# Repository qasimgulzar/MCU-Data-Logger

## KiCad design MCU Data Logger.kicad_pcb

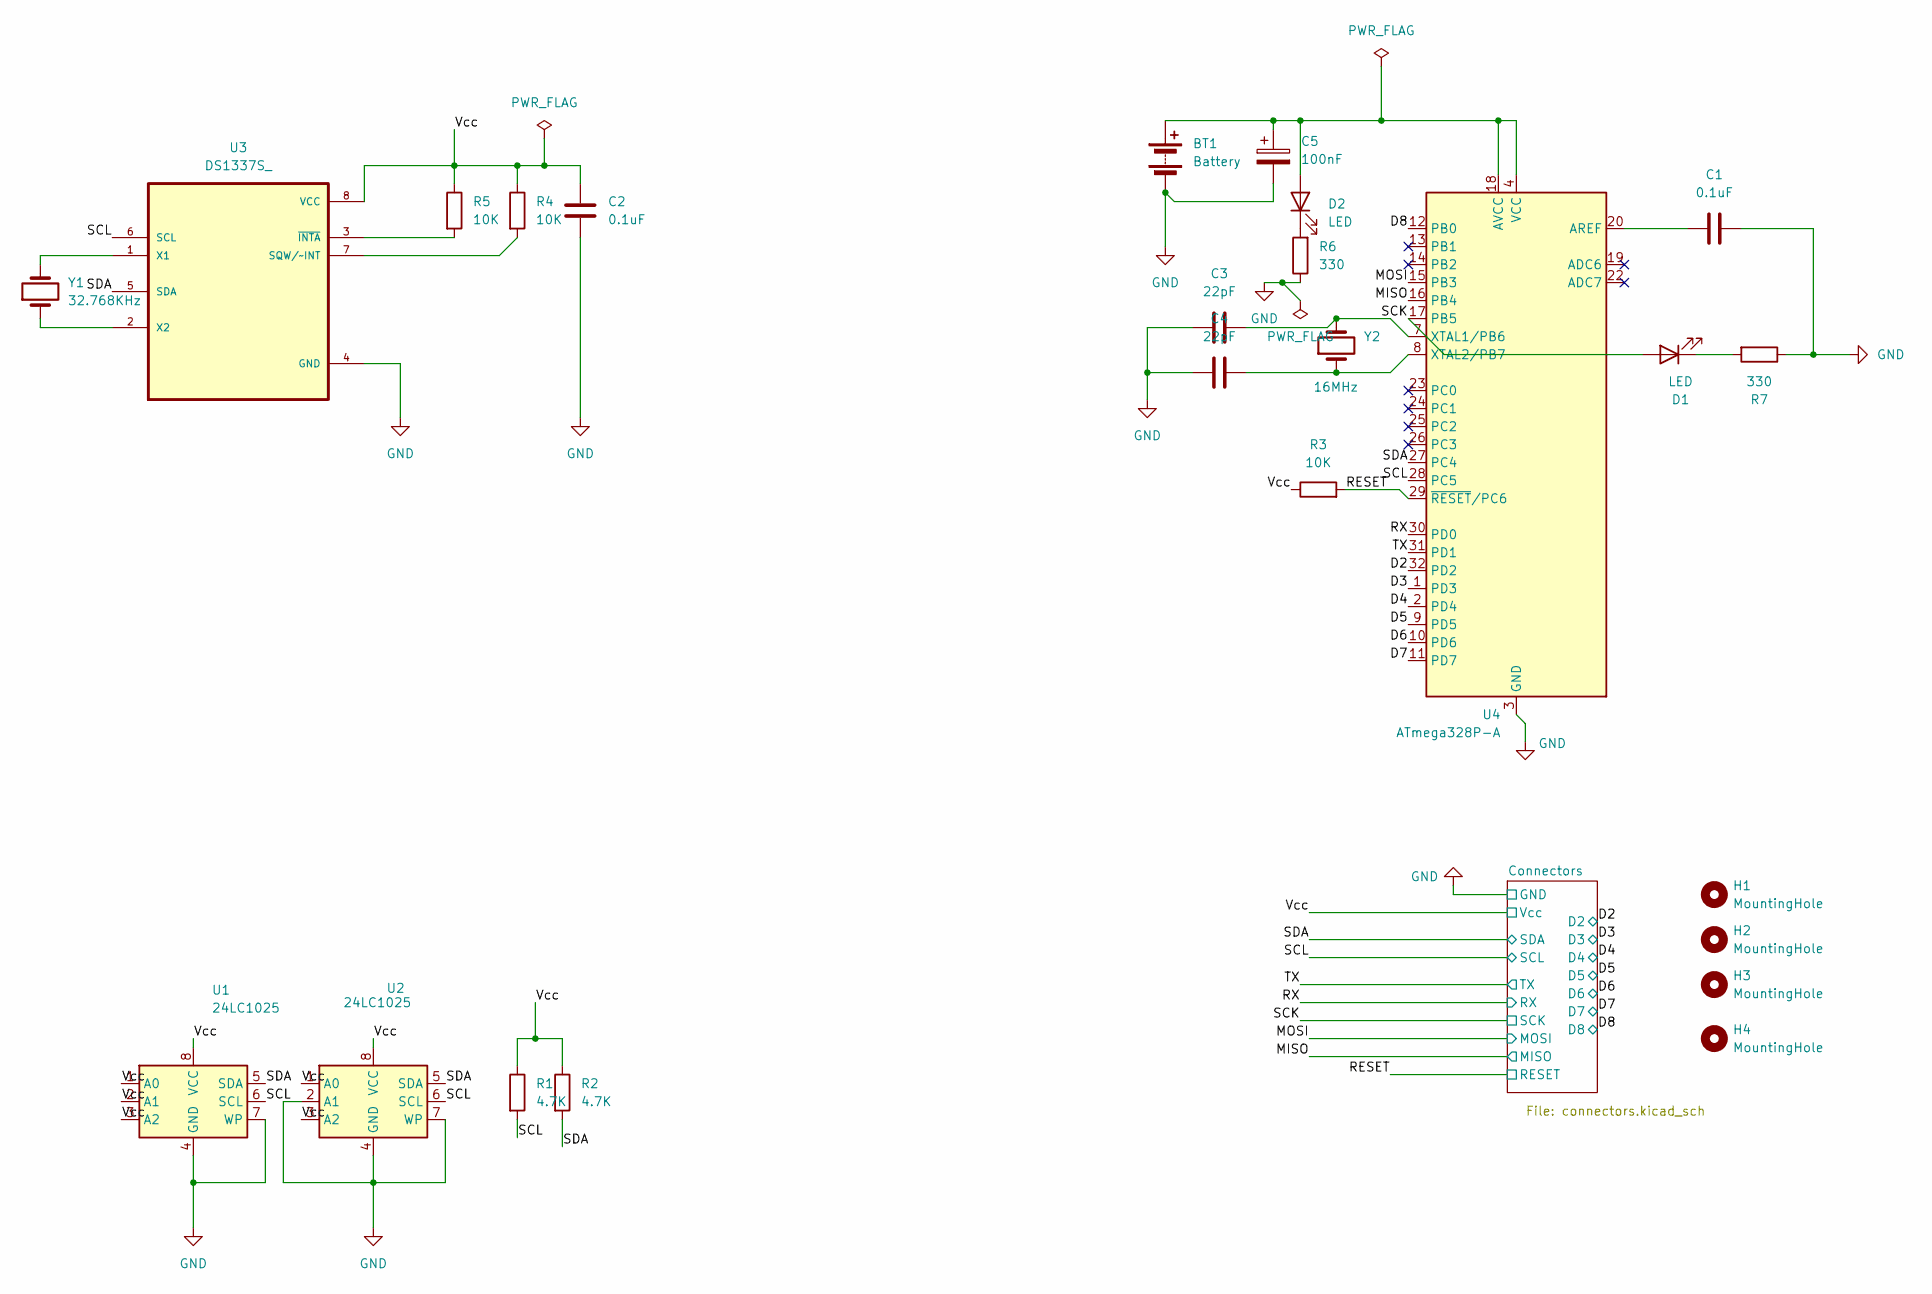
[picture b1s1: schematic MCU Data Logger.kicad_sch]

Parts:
BT1: Battery; PinHeader_1x02_P2.54mm_Vertical
C1, C2: 0.1uF; C_0805_2012Metric
C3, C4: 22pF; C_0805_2012Metric
C5: 100nF; C_0805_2012Metric
D1, D2: LED; LED_0805_2012Metric
H1, H2, H3, H4: MountingHole; MountingHole_2.1mm
R1, R2: 4.7K; R_0805_2012Metric
R3, R4, R5: 10K; R_0805_2012Metric
R6, R7: 330; R_0805_2012Metric
U1, U2: 24LC1025; SOIC-8_5.3x5.3mm_P1.27mm
U3: DS1337S_; SOIC127P600X175-8N
U4: ATmega328P-A; LQFP-32_7x7mm_P0.8mm
Y1: 32.768KHz; Crystal_SMD_5032-2Pin_5.0x3.2mm
Y2: 16MHz; Crystal_SMD_5032-2Pin_5.0x3.2mm

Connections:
/D2: U4.32 (PD2); also elsewhere on the board
/D3: U4.1 (PD3); also elsewhere on the board
/D4: U4.2 (PD4); also elsewhere on the board
/D5: U4.9 (PD5); also elsewhere on the board
/D6: U4.10 (PD6); also elsewhere on the board
/D7: U4.11 (PD7); also elsewhere on the board
/D8: U4.12 (PB0); also elsewhere on the board
/MISO: U4.16 (PB4); also elsewhere on the board
/MOSI: U4.15 (PB3); also elsewhere on the board
/RESET: R3.2, U4.29 (~RESET/PC6); also elsewhere on the board
/RX: U4.30 (PD0); also elsewhere on the board
/SCK: D1.2 (A), U4.17 (PB5); also elsewhere on the board
/SCL: R1.2, U1.6 (SCL), U2.6 (SCL), U3.6 (SCL), U4.28 (PC5); also elsewhere on the board
/SDA: R2.2, U1.5 (SDA), U2.5 (SDA), U3.5 (SDA), U4.27 (PC4); also elsewhere on the board
/TX: U4.31 (PD1); also elsewhere on the board
/Vcc: C2.1, R1.1, R2.1, R3.1, R4.1, R5.1, U1.1 (A0), U1.2 (A1), U1.3 (A2), U1.8 (VCC), U2.1 (A0), U2.3 (A2), U2.8 (VCC), U3.8 (VCC); also elsewhere on the board
GND: BT1.2 (-), C1.2, C2.2, C3.2, C4.1, C5.2, R6.1, R7.1, U1.4 (GND), U1.7 (WP), U2.2 (A1), U2.4 (GND), U2.7 (WP), U3.4 (GND), U4.3 (GND), U4.5 (GND), U4.21 (GND); also elsewhere on the board
unnamed: BT1.1 (+), C5.1, D2.2 (A), U4.4 (VCC), U4.6 (VCC), U4.18 (AVCC)
unnamed: D1.1 (K), R7.2
unnamed: D2.1 (K), R6.2
unnamed: R4.2, U3.7 (SQW/~INT)
unnamed: U3.1 (X1), Y1.2
unnamed: U3.2 (X2), Y1.1
unnamed: R5.2, U3.3 (~INTA)
unnamed: C1.1, U4.20 (AREF)
unnamed: C3.1, U4.7 (XTAL1/PB6), Y2.2
unnamed: C4.2, U4.8 (XTAL2/PB7), Y2.1

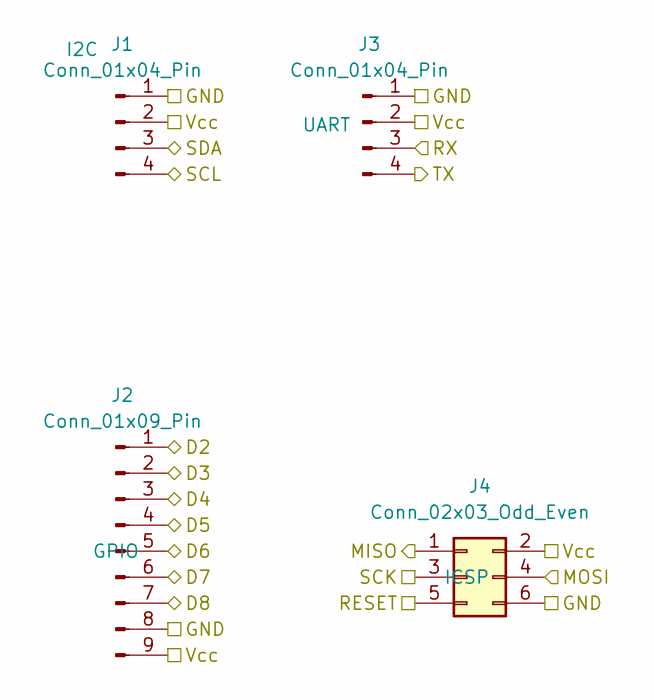
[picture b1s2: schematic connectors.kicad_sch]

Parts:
J1, J3: Conn_01x04_Pin; PinHeader_1x04_P2.54mm_Vertical
J2: Conn_01x09_Pin; PinHeader_1x09_P2.54mm_Vertical
J4: Conn_02x03_Odd_Even; PinHeader_2x03_P2.54mm_Vertical

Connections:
/D2: J2.1; also elsewhere on the board
/D3: J2.2; also elsewhere on the board
/D4: J2.3; also elsewhere on the board
/D5: J2.4; also elsewhere on the board
/D6: J2.5; also elsewhere on the board
/D7: J2.6; also elsewhere on the board
/D8: J2.7; also elsewhere on the board
/MISO: J4.1; also elsewhere on the board
/MOSI: J4.4; also elsewhere on the board
/RESET: J4.5; also elsewhere on the board
/RX: J3.3; also elsewhere on the board
/SCK: J4.3; also elsewhere on the board
/SCL: J1.4; also elsewhere on the board
/SDA: J1.3; also elsewhere on the board
/TX: J3.4; also elsewhere on the board
/Vcc: J1.2, J2.9, J3.2, J4.2; also elsewhere on the board
GND: J1.1, J2.8, J3.1, J4.6; also elsewhere on the board

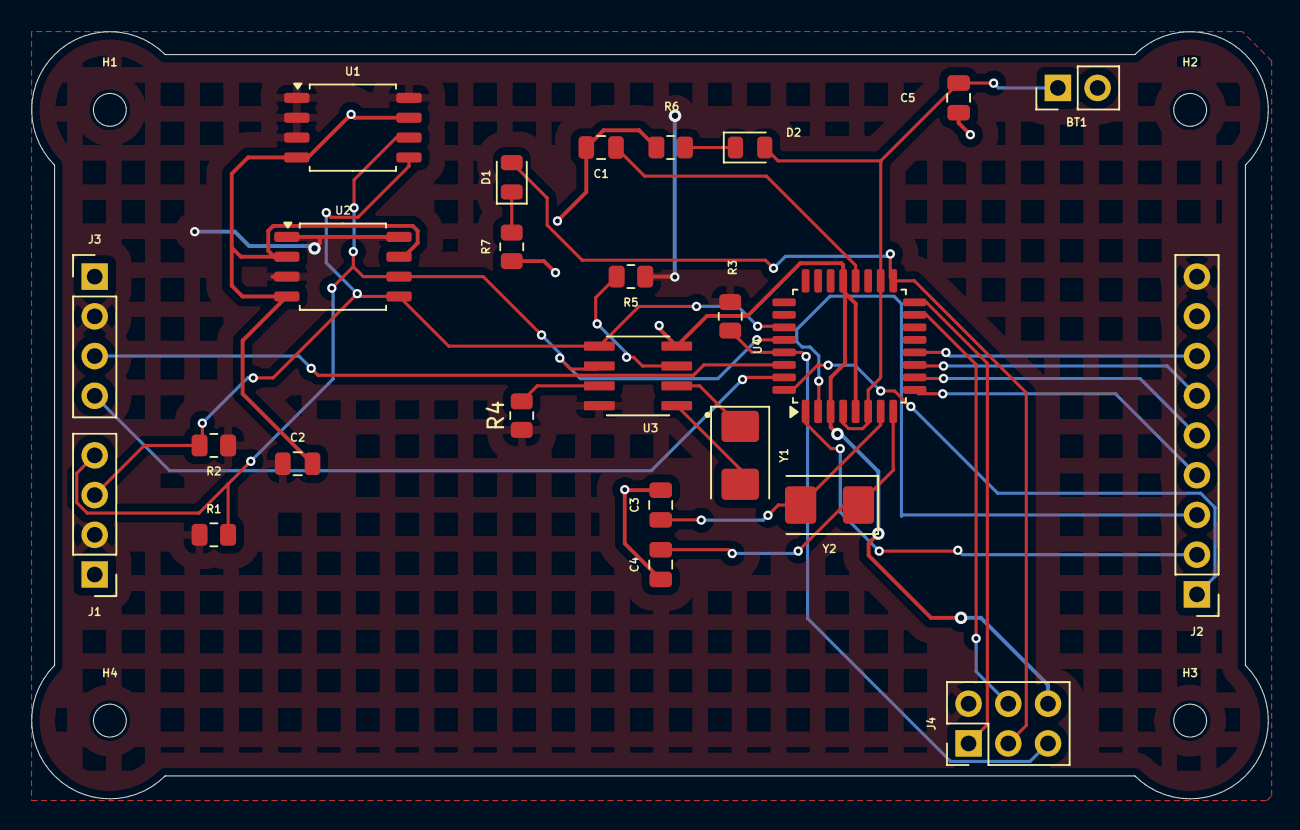
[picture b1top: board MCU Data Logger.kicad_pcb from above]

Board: 2 copper layers, 79.1 x 49.1 mm, 29 parts (0 on the bottom side), 27 nets.

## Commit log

2025-09-13 project init
2025-09-13 all required symbols
2025-09-13 updated values
2025-09-13 wiring complete
2025-09-13 complete PCB
2025-09-14 bug fix
